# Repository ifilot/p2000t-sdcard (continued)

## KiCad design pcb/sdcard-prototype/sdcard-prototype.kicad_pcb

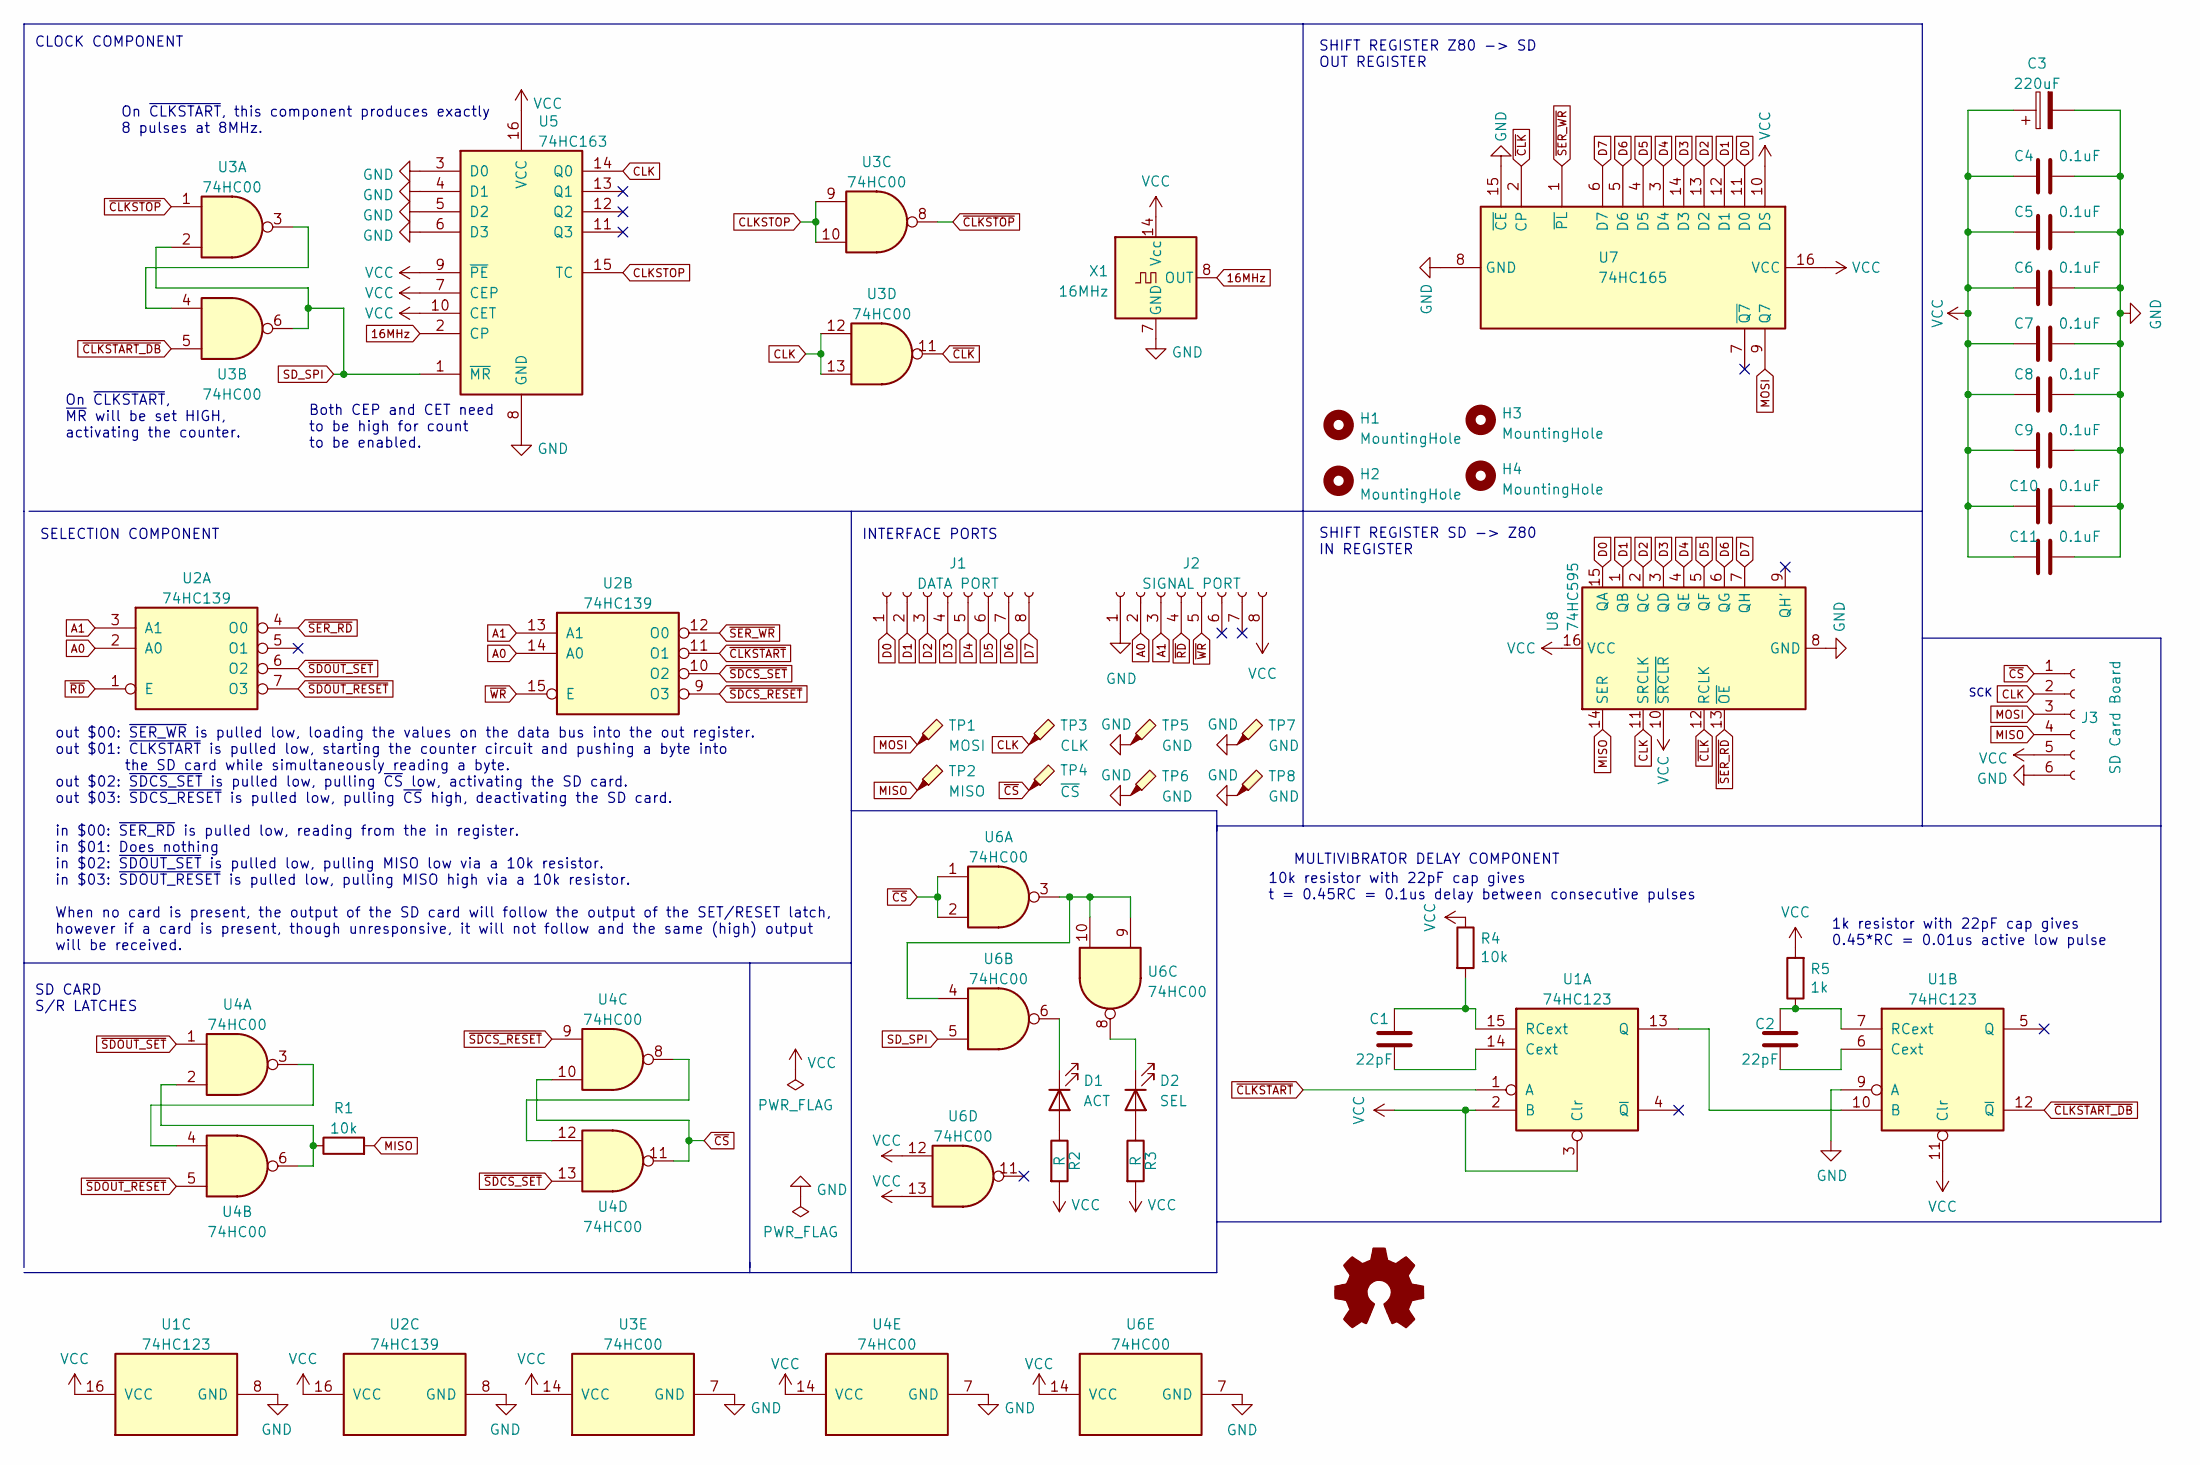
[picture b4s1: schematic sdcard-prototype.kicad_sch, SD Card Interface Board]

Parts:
C1, C2: 22pF; C_Disc_D5.0mm_W2.5mm_P5.00mm
C3: 220uF; CP_Radial_D6.3mm_P2.50mm
C4, C5, C6, C7, C8, C9, C10, C11: 0.1uF; C_Disc_D5.0mm_W2.5mm_P5.00mm
D1: ACT; LED_D5.0mm
D2: SEL; LED_D5.0mm
H1, H2, H3, H4: MountingHole; MountingHole_3.2mm_M3_DIN965
J1: DATA PORT; PinSocket_1x08_P2.54mm_Vertical
J2: SIGNAL PORT; PinSocket_1x08_P2.54mm_Vertical
J3: SD Card Board; PinSocket_1x06_P2.54mm_Vertical
R1, R4: 10k; R_Axial_DIN0207_L6.3mm_D2.5mm_P7.62mm_Horizontal
R2, R3: R; R_Axial_DIN0207_L6.3mm_D2.5mm_P7.62mm_Horizontal
R5: 1k; R_Axial_DIN0207_L6.3mm_D2.5mm_P7.62mm_Horizontal
TP1: MOSI; TestPoint_THTPad_2.5x2.5mm_Drill1.2mm
TP2: MISO; TestPoint_THTPad_2.5x2.5mm_Drill1.2mm
TP3: CLK; TestPoint_THTPad_2.5x2.5mm_Drill1.2mm
TP4: ~{CS}; TestPoint_THTPad_2.5x2.5mm_Drill1.2mm
TP5, TP6, TP7, TP8: GND; TestPoint_Pad_4.0x4.0mm
U1: 74HC123; DIP-16_W7.62mm_Socket
U2: 74HC139; DIP-16_W7.62mm_Socket
U3, U4, U6: 74HC00; DIP-14_W7.62mm_Socket
U5: 74HC163; DIP-16_W7.62mm_Socket
U7: 74HC165; DIP-16_W7.62mm_Socket
U8: 74HC595; DIP-16_W7.62mm_Socket
X1: 16MHz; Oscillator_DIP-14

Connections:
16MHz: U5.2 (CP), X1.8 (OUT)
A0: J2.2, U2.2 (A0), U2.14 (A0)
A1: J2.3, U2.3 (A1), U2.13 (A1)
CLK: J3.2, TP3.1, U3.12, U3.13, U5.14 (Q0), U8.11 (SRCLK)
CLKSTOP: U3.9, U3.10, U5.15 (TC)
D0: J1.1, U7.11 (D0), U8.15 (QA)
D1: J1.2, U7.12 (D1), U8.1 (QB)
D2: J1.3, U7.13 (D2), U8.2 (QC)
D3: J1.4, U7.14 (D3), U8.3 (QD)
D4: J1.5, U7.3 (D4), U8.4 (QE)
D5: J1.6, U7.4 (D5), U8.5 (QF)
D6: J1.7, U7.5 (D6), U8.6 (QG)
D7: J1.8, U7.6 (D7), U8.7 (QH)
GND: C3.2, C4.2, C5.2, C6.2, C7.2, C8.2, C9.2, C10.2, C11.2, J2.1, J3.6, TP5.1, TP6.1, TP7.1, TP8.1, U1.8 (GND), U1.9 (A), U2.8 (GND), U3.7 (GND), U4.7 (GND), U5.3 (D0), U5.4 (D1), U5.5 (D2), U5.6 (D3), U5.8 (GND), U6.7 (GND), U7.8 (GND), U7.15 (~CE), U8.8 (GND), X1.7 (GND)
MISO: J3.4, R1.2, TP2.1, U8.14 (SER)
MOSI: J3.3, TP1.1, U7.9 (Q7)
unnamed: C1.1, U1.14 (Cext)
unnamed: C1.2, R4.2, U1.15 (RCext)
unnamed: C2.1, U1.6 (Cext)
unnamed: C2.2, R5.1, U1.7 (RCext)
unnamed: D1.1 (K), U6.6
unnamed: D1.2 (A), R2.1
unnamed: D2.1 (K), U6.8
unnamed: D2.2 (A), R3.1
unnamed: R1.1, U4.2, U4.6
unnamed: U1.10 (B), U1.13 (Q)
unnamed: U3.3, U3.4
unnamed: U4.3, U4.4
unnamed: U4.8, U4.12
unnamed: U6.3, U6.4, U6.9, U6.10
SD_SPI: U3.2, U3.6, U5.1 (~MR), U6.5
VCC: C3.1, C4.1, C5.1, C6.1, C7.1, C8.1, C9.1, C10.1, C11.1, J2.8, J3.5, R2.2, R3.2, R4.1, R5.2, U1.2 (B), U1.3 (Clr), U1.11 (Clr), U1.16 (VCC), U2.16 (VCC), U3.14 (VCC), U4.14 (VCC), U5.7 (CEP), U5.9 (~PE), U5.10 (CET), U5.16 (VCC), U6.12, U6.13, U6.14 (VCC), U7.10 (DS), U7.16 (VCC), U8.10 (~SRCLR), U8.16 (VCC), X1.14 (Vcc)
~CLKSTART_DB: U1.12 (~Q), U3.5
~CLKSTART: U1.1 (A), U2.11 (O1)
~CLKSTOP: U3.1, U3.8
~CLK: U3.11, U7.2 (CP), U8.12 (RCLK)
~CS: J3.1, TP4.1, U4.10, U4.11, U6.1, U6.2
~RD: J2.4, U2.1 (E)
~SDCS_RESET: U2.9 (O3), U4.9
~SDCS_SET: U2.10 (O2), U4.13
~SDOUT_RESET: U2.7 (O3), U4.5
~SDOUT_SET: U2.6 (O2), U4.1
~SER_RD: U2.4 (O0), U8.13 (~OE)
~SER_WR: U2.12 (O0), U7.1 (~PL)
~WR: J2.5, U2.15 (E)

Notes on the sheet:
SHIFT REGISTER SD -> Z80 IN REGISTER
SD CARD S/R LATCHES
out $00: ~{SER_WR} is pulled low, loading the values on the data bus into the out register. out $01: ~{CLKSTART} is pulled low, starting the counter circuit and pushing a byte into the SD card while simultaneously reading a byte. out $02: ~{SDCS_SET} is pulled low, pulling ~{CS} low, activating the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
On ~{CLKSTART}, this component produces exactly 8 pulses at 8MHz.
On ~{CLKSTART}, ~{MR} will be set HIGH, activating the counter.
in $00: ~{SER_RD} is pulled low, reading from the in register. in $01: Does nothing in $02: ~{SDOUT_SET} is pulled low, pulling MISO low via a 10k resistor. in $03: ~{SDOUT_RESET} is pulled low, pulling MISO high via a 10k resistor. When no card is present, the output of the SD card will follow the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
SELECTION COMPONENT
1k resistor with 22pF cap gives 0.45*RC = 0.01us active low pulse
10k resistor with 22pF cap gives t = 0.45RC = 0.1us delay between consecutive pulses
CLOCK COMPONENT
INTERFACE PORTS
Both CEP and CET need to be high for count to be enabled.
SCK
MULTIVIBRATOR DELAY COMPONENT
SHIFT REGISTER Z80 -> SD OUT REGISTER

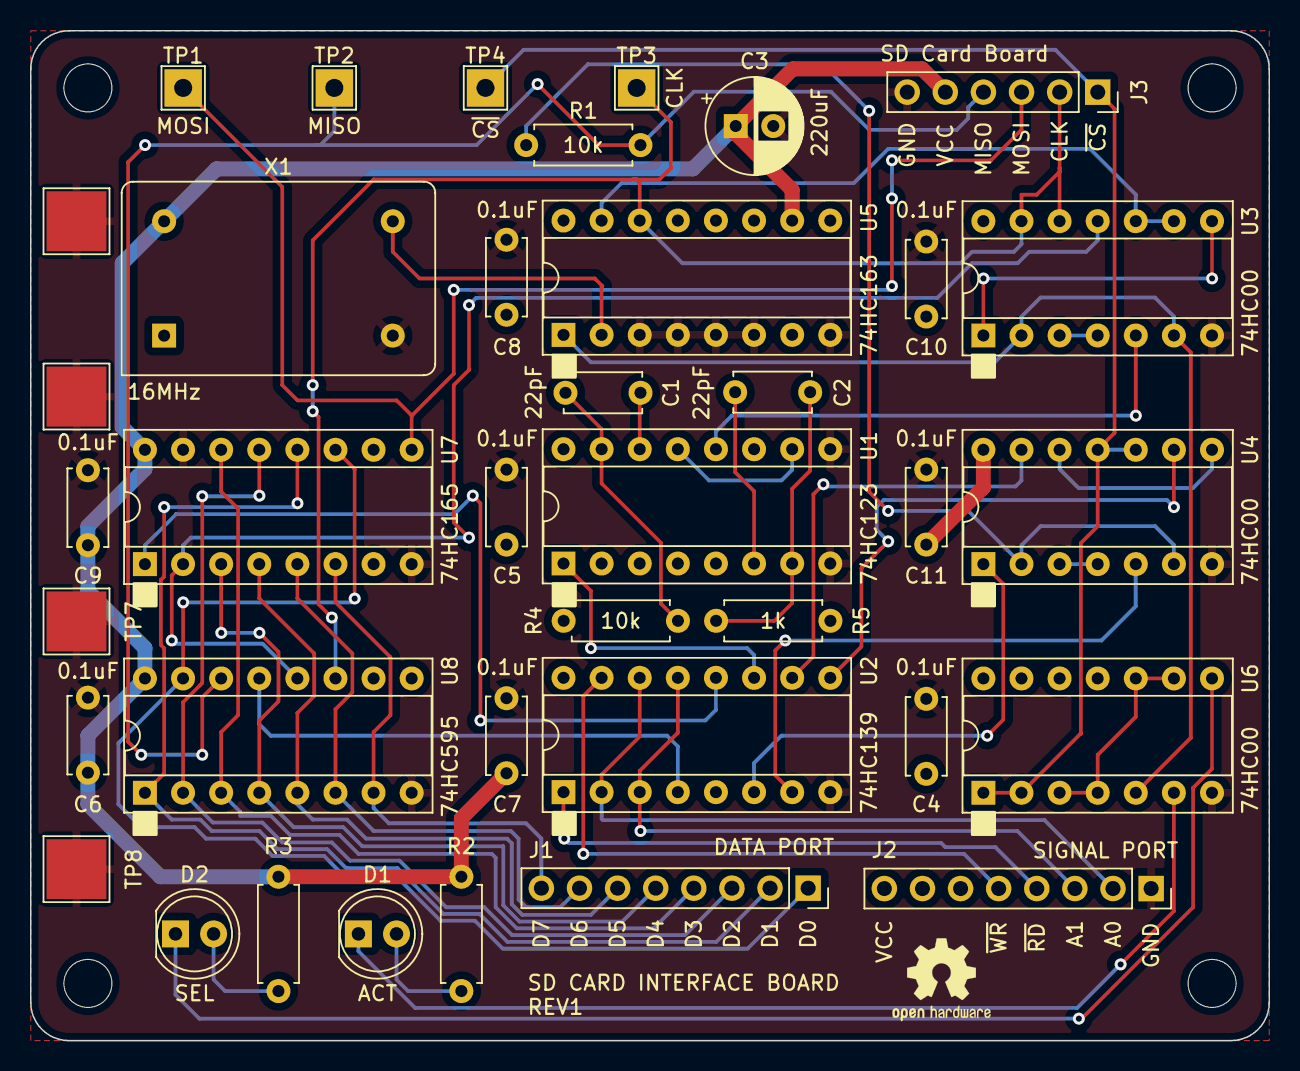
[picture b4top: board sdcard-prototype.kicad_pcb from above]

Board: 2 copper layers, 82.5 x 67.3 mm, 42 parts (0 on the bottom side), 45 nets.

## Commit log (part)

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2024-03-17 Adding images
2024-03-17 Reformatting
2024-03-17 Fixing image
2024-03-17 Adding BASICROM
2024-03-17 Creating multirom cartridge
2024-03-17 Fixing path
2024-03-17 Fix bug in still showing unused directory entries
2024-03-17 Version 0.1.1 (#1)
    * Creating multirom cartridge
    * Fixing path
    * Fix bug in still showing unused directory entries
    * Fix bug in still showing unused directory entries
2024-03-17 Adding XOR a before RUN
2024-03-25 Adding secondary LEDs
2024-03-26 Fixing bug in RAM/ROM leds
2024-04-08 Adding LEDs in software and improvSD card assembly routines
2024-04-08 LEDs and improved SD card assembly rountines (#2)
    * Adding secondary LEDs
    * Fixing bug in erroneously triggered LEDs
    * Fixing bug in RAM/ROM leds
    * Update config.h
    * Adding LEDs in software and improvSD card assembly routines
2024-04-08 Incrementing version number
2024-04-09 Revising PCB
2024-04-10 Improving cases
2024-04-20 Showing partition volume name
2024-04-20 Polishing internal RAM routines
2024-04-20 Adding comments
2024-04-20 Fixing Makefile adjustment
2024-04-20 Improved external RAM copying routines (#3)
    * Showing partition volume name
    * Polishing internal RAM routines
    * Adding comments
    * Adding custom copy routines for SD-card to external RAM
    * Fixing Makefile adjustment
2024-04-20 Revising build procedure
2024-04-20 Changing filename
2024-04-20 Changing compilation depth
2024-04-20 Fixing bug in deployment (#4)
    * Revising build procedure
    * Changing filename
    * Changing compilation depth
2024-04-26 Adding 4mm inserts
2024-04-27 Modifying case and changing flasher to also accept SST39SF020 SST39SF040 chips
2024-04-27 Changing PCB to also accept SST39SF020 and SST39SF040 chips
2024-04-29 Adding byte replacement function
2024-04-30 Refactoring C to assembly
2024-04-30 Further refactoring SD-card routines
2024-04-30 Further pruning functions and migrating SD card routines to assembly
2024-05-01 Migrating SD card buffer to external RAM and fixing lscas command
2024-05-01 Changing resistor value
2024-05-01 Reintroducing LEDtest and hexdump
2024-05-01 Expanding README
2024-05-01 Adding badges
2024-05-01 Fixing bugs in Flasher
2024-05-01 Signing launcher firmware
2024-05-01 Changing ordeR
2024-05-01 Refactoring code and changing GA
2024-05-01 Adding comments and fixing lscas command
2024-05-01 Patch v0.5.0 (#6)
    * Signing launcher firmware
    * Fix
    * Changing ordeR
    * Refactoring code and changing GA
    * Adding comments and fixing lscas command
2024-05-02 Removing checksum upload
2024-05-02 Adding memory model
2024-05-02 Allowing execution of custom programs from SD card
2024-05-02 Further pruning obsolete files
2024-05-02 Replacing front images
2024-05-02 Expanding README.md
2024-05-02 Revising image
2024-05-02 Allowing launching of external programs
2024-05-04 Showing partition size and removing less relevant data
2024-05-04 Fixing typos
2024-05-05 Adding hexdumps for ROM, RAM and main memory
2024-05-05 Adding CRC16 check for monitor and shuffling routines
2024-05-10 Adding routine to test for the presence of an SD-card
2024-05-10 Compiling programs
2024-05-10 Signing
2024-05-10 Packaging programs
2024-05-10 Listing files
2024-05-10 Fixing
2024-05-10 Fix unique name issue
2024-05-10 Attempt 2
2024-05-10 Different zipping
2024-05-10 Expanding README.md file
2024-05-10 Adding OSHW logo
2024-05-10 Patch v0.6.0 (#7)
    * Adding memory model
    * Allowing execution of custom programs from SD card
    * Removing wrong files
    * Further pruning obsolete files
    * Replacing front images
    * Expanding README.md
2024-05-10 Adding license tag
2024-05-10 Fixing GA
2024-05-12 Adding warning
2024-05-26 Setting port addresses in header and include files
2024-05-26 Updating rev and changing 0x60 to 0x40
2024-05-26 Changing port for BASICmod
2024-05-26 Retrying connecting to SD card
2024-05-26 Retrying connecting to SD card on failed attempt (#8)
    * Adding memory model
    * Allowing execution of custom programs from SD card
    * Removing wrong files
    * Further pruning obsolete files
    * Replacing front images
    * Expanding README.md
2024-05-27 Adding enclosure files, changing CI and adding option to disable hardware test
2024-05-27 Fixing CI
2024-05-27 Adding README.md
2024-05-27 PCB revision 6 (#9)
    * Setting port addresses in header and include files
    * Updating rev and changing 0x60 to 0x40
    * Changing port for BASICmod
    * Incrementing version number
    * Adding enclosure files, changing CI and adding option to disable hardware test
    * Fixing CI
2024-05-27 Fixing build procedure and README.md
2024-05-27 Fixing README.md
2024-06-08 Removing SD-card detection routines
2024-06-08 Creating separate SD-CARD test cartridge and modifying SD-card detection routine
2024-06-08 Updating license
2024-06-29 Creating 512k multirom image
2024-06-29 Fixing suffixes
2024-06-29 Splitting release upload
2024-06-29 Removing incorrect dependency
2024-06-29 Adding indent
2024-06-29 Yet another attempt
2024-06-29 Using BASH file
2024-06-29 Fixing output file
2024-06-29 Adding card creation
2024-06-29 Adjusting name
2024-06-29 Fixing identation
2024-06-29 Adding checkout
2024-06-29 Creation of multirom image (#10)
    * Creating 512k multirom image
    * Fixing suffixes
    * Splitting release upload
    * Removing incorrect dependency
    * Adding indent
    * Yet another attempt
2024-06-29 Incrementing version
2024-07-05 Initial commit SD-card dumper
2024-07-17 Adding help command
2024-07-19 Revising README.md
2024-07-19 Refactoring print functions
2024-07-19 Patch v0.7.4 (#11)
    * Initial commit SD-card dumper
    * Adding help command
    * Revising README.md
    * Fixing bug in hex to uint16t conversion
    * Refactoring print functions
2024-07-21 Expanding documentation and showing PCB layout
2024-07-22 Initial commit diagnostics cartridge and fixing bug allowing for more diverse sd-cards.
2024-07-22 Removing map file
2024-07-22 Fix bug in reporting partition capactities
2024-07-24 Finding file and folders in diag cartridge
2024-07-24 Polishing output
2024-07-24 Storing writetest
2024-07-24 Adding explanation to test
2024-07-25 Creating BOM/CPL for assembly service
2024-07-25 ReOptimizing instructions
2024-07-25 End of day commit
2024-07-26 Timeout and data errors
2024-07-27 Succesfully creating new file
2024-07-27 Polishing FAT32 routines
2024-07-27 Further polishing code
2024-07-27 Adding file pointer creation
2024-07-28 Writing data to SD card
2024-07-28 Initial commit cassette dump cartridge
2024-07-29 Dumping cassette to SD-card
2024-07-30 Further polishing code for cassette dump
2024-07-31 Refactoring repo
2024-07-31 Polishing cassette dump utility
2024-07-31 Fixing bug reading invalid folder
2024-07-31 Adding casdump to GA
2024-07-31 Adding csv files
2024-07-31 Version 0.8.0 (#13)
    * Initial commit diagnostics cartridge and fixing bug allowing for more diverse sd-cards.
    * Removing map file
    * Fix bug in reporting partition capactities
    * Finding file and folders in diag cartridge
    * Polishing output
    * Storing writetest
2024-08-02 Adding 0x60 variant for CASDUMP
2024-08-02 Fixing dependency
2024-08-02 Patch 0.8.1 (#14)
    * Adding 0x60 variant for CASDUMP
    * Fixing dependency
2024-08-02 Replacing release action
2024-08-02 Replacing tag
2024-08-02 Another attempt inserting the tag
2024-08-02 Fixing CASDUMP
2024-08-02 Fixing reference
2024-08-04 Updating session
2024-08-04 Finalizing rev0
2024-08-16 Adding brackets
2024-08-18 Small revision of miniboard and enabling autoboot function
2024-09-14 Adding image
2024-09-14 Miniboard (#15)
    * Preflight
    * Updating session
    * Finalizing rev0
    * Adding brackets
    * Small revision of miniboard and enabling autoboot function
    * Adding image
2024-10-19 Increasing hole depth
2024-10-22 Fixing label
2024-10-22 Tuning enclosure
2024-11-10 Adding YouTube movie
2024-12-10 Fixing value in schematic
2025-01-02 Removing copper pour around edge connector
2025-01-02 Removing copper pour around edge connector (#17)
2025-01-06 Improving case
2025-01-10 Using a single hook into Basic for running custom code at startup
2025-01-10 small documentation change
2025-01-12 Using cropped and jpg variant
2025-01-12 Removing 0x60 version
2025-01-12 Removing building multiroms
2025-01-12 Release v1.0.0 (#19)
    * Removing 0x60 version
    * Removing building multiroms
    * Updating README.md
    * Incrementing version number
2025-01-12 Migrating PRG programs to different repository
2025-01-12 Fixing Github Actions
2025-01-12 Adapting patches to PR
2025-01-12 Action build fix
2025-01-13 Integrating discord
2025-01-13 Rewriting message
2025-01-13 Initial commit documentation
2025-01-13 Changing Python version
2025-01-13 deploy: 7975ef1435ba5c44af51091ea861899a727b83f7
2025-01-13 basicmod refactorings incl SP relocation
2025-01-13 minor change to trigger github build Actions
2025-01-14 Added 'load' command and PRG support for 16K machines
2025-01-14 Better visual allignment addresses
2025-01-14 Flashing "any key" to make it stand out
2025-01-14 using macro for reading program metadata
2025-01-14 Initial changes for release 2 (#20)
    * Integrating discord
    * Rewriting message
    * basicmod refactorings incl SP relocation
    * minor change to trigger github build Actions
    * Added 'load' command and PRG support for 16K machines
    * Better visual allignment addresses
2025-01-14 New Launcher max length is 15.031 + SP fixed to $6200
2025-01-14 Creating release 2.x branch with latest development version
2025-01-14 Fixing v2.yml
2025-01-14 Creating a latest-stable workflow
2025-01-14 Requiring NumPy
2025-01-14 Creating a latest-stable workflow (#22)
    * Creating a latest-stable workflow
    * Requiring NumPy
2025-01-14 Incrementing version to 2.0
2025-01-14 Modyfing enclosure as 0x40 variant is now implied
2025-01-17 Learned about Z80's `ex` command recently
2025-01-17 Learned about Z80's `ex` command recently (#27)
2025-01-21 Update latest-stable.yml
    Prevent deploy-job from running on forks
2025-01-22 Update latest-stable.yml (#28)
    Prevent deploy-job from running on forks
2025-01-22 Added devcontainer + only deploy if repo owner is 'ifilot' (#29)
2025-02-11 Launcher uses long file names
2025-02-12 changed `filename` to `_filename` as it's a global var
2025-05-26 launcher 1.1.0
    - long filename support
    - `load` command to load a .cas to memory and return to Basic
    - `crc` command to calculate CRC16 checksum
    - error when .cas is too large to load into available memory
2025-05-27 fix in relocated loadrom code
2025-05-27 relocation offset refactor
2025-05-27 action-gh-release fix?
2025-05-27 PR's should fire latest-stable build/deploys
2025-05-28 extracted the launch_cas asm code
2025-05-29 Launcher 1.1.0 (#34)
    # Launcher v1.1.0
    * long filename support
    * `load` command to load a .cas to memory and return to Basic
    * `crc` command to calculate CRC16 checksum
    * error when .cas is too large to load into available memory
    * fix in relocated loadrom code
2025-05-29 Removing latest-stable
2025-05-29 Updating links
2025-06-06 introducing Easy-Launcher
2025-06-06 Added EZLAUNCH to Github Build
2025-06-06 Added more comments
2025-06-06 last moment bug fix :)
2025-06-07 Adding easy-launch, thus incrementing version
2025-06-08 added new flash command
2025-06-08 Initial commit GEN2 variant of PCB
2025-06-08 After flash, wait for key and reboot
2025-06-08 easy-launcher using same version
2025-06-08 flash fix
2025-06-08 clearing key buffer on start
2025-06-08 Initial prototype schematic
2025-06-08 Initial placement components
2025-06-08 easy launcher now also supports AUTOBOOT.CAS
2025-07-05 fixes showing of hidden system files/folders like 'System Volume Information'
2025-07-06 fixes showing of hidden system files/folders like 'System Volume Information' (#37)
